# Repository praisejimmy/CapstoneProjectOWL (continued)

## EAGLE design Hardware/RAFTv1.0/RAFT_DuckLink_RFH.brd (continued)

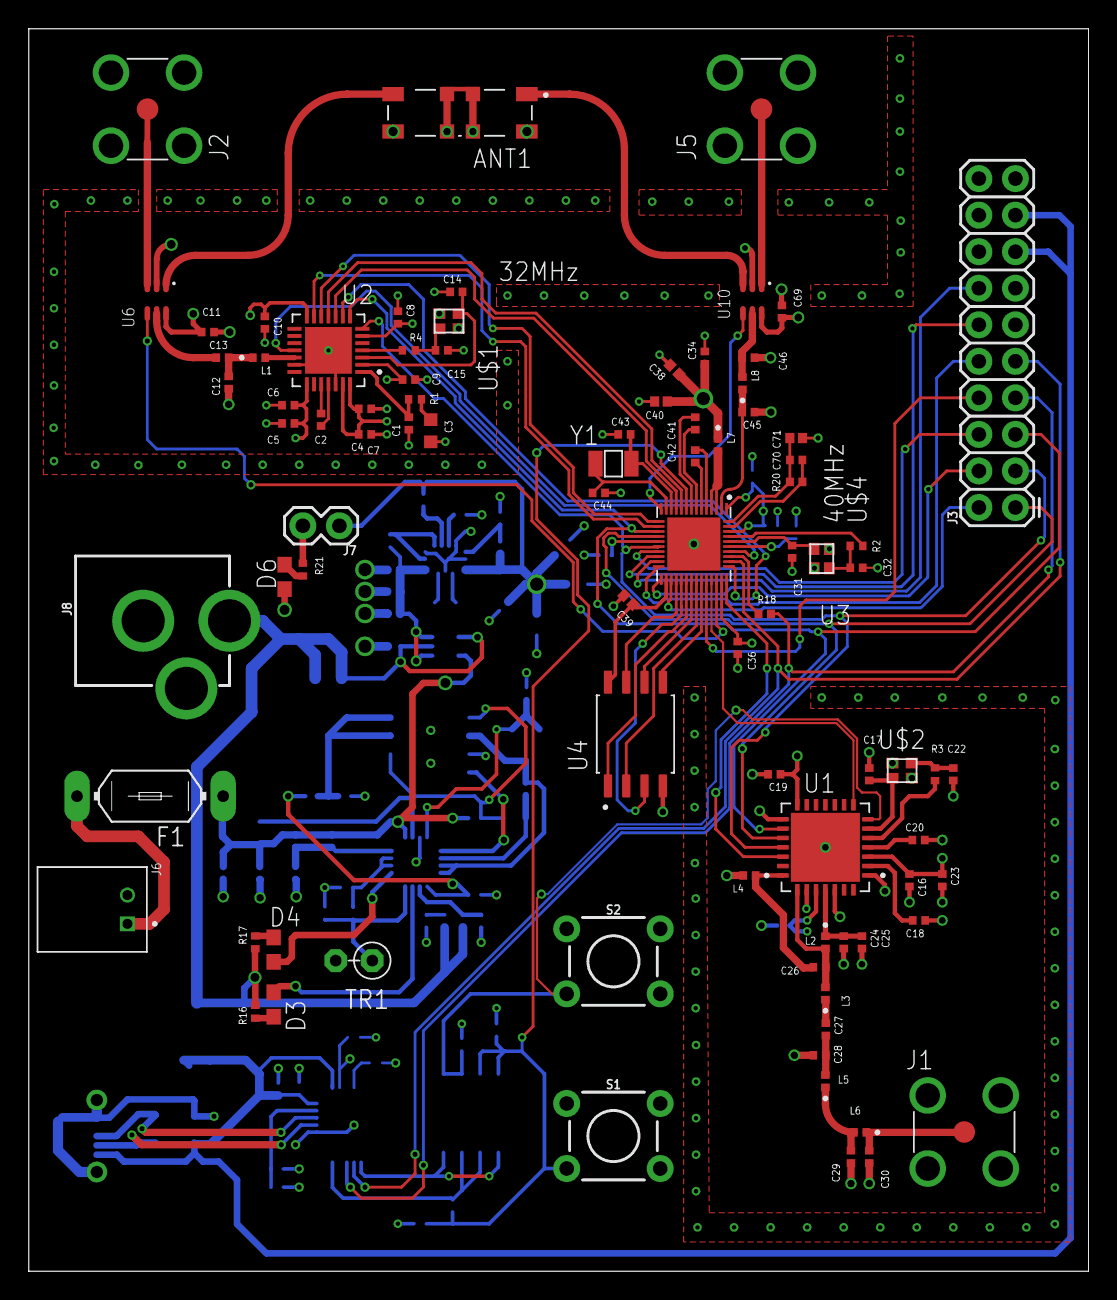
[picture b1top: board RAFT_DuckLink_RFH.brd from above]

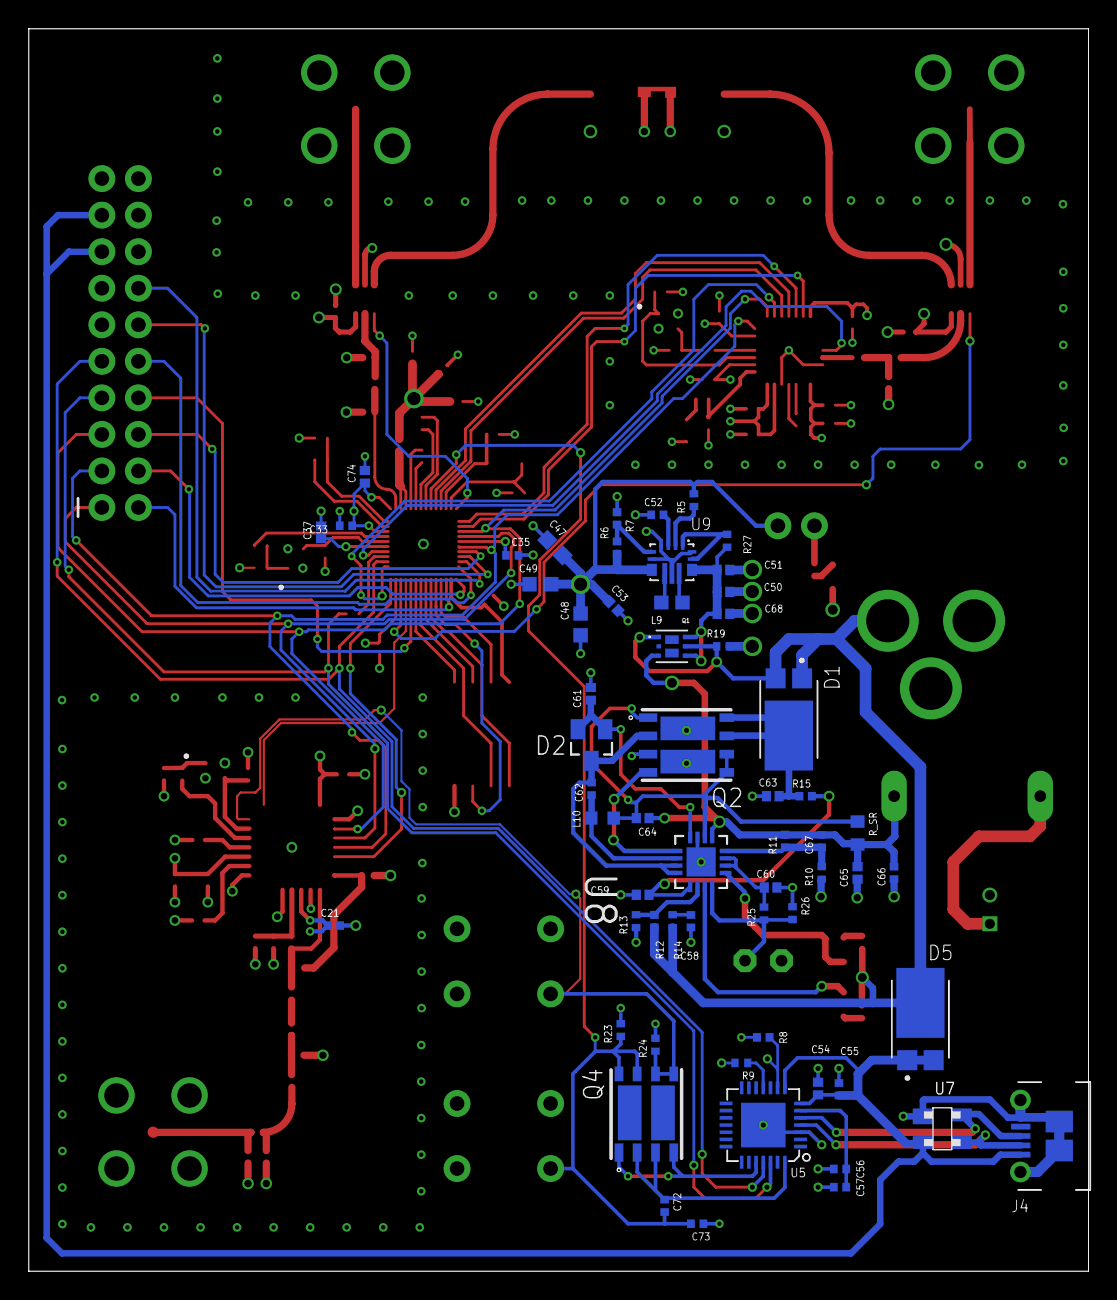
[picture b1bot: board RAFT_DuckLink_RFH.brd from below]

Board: 4 copper layers, 73.7 x 86.4 mm, 147 parts (60 on the bottom side), 111 nets.

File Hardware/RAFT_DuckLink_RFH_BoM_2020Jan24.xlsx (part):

Qty | Value | Device | Package | Ref Des | Description | DIGI-KEY_PART_NUMBER | DIGI-KEY_PURCHASE_URL | MF | MPN | PACKAGE.1
18 | 0.1uF | GCM155R71C104KA55J | CAPC1005X55N | C4, C6, C7, C8, C9, C10, C16, C18, C19, C20, C21, C34, C35, C36, C52, C55, C56,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 | Cap Ceramic 0.1uF 16V X7R 10% Pad SMD 0402 125Â°C Automotive T/R | 490-7998-1-ND | https://www.digikey.com/product-detail/en/murata-electronics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 | Murata | GCM155R71C104KA55J | 1005 Taiyo Yuden
3 | 0R | CRCW04020000Z0ED | RESC1005X40N | R2, R3, R4 | RESISTOR, 0402, 0R, FULL REEL | 541-0.0JCT-ND | https://www.digikey.com/product-detail/en/vishay-dale/CRCW04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 | Vishay | CRCW04020000Z0ED | 1005 Panasonic Electronic Components
4 | 1.0uF | GCM155C71A105KE38D | CAPC1005X70N | C54, C59, C60, C61 | Cap Ceramic 1uF 10V X7S 10% Pad SMD 0402 125C Automotive T/R |  |  | Murata | GCM155C71A105KE38D | 1005 Murata
1 | 1.5pF | GCM1555C1H1R5JA16D | CAPC1005X55N | C26 | CAP AUTO-GRADE 1.5PF 50VDC C0G 5% SMD 0402 | 490-16452-1-ND | https://www.digikey.com/product-detail/en/murata-electronics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 | Murata Electronics | GCM1555C1H1R5JA16D | 1005 Taiyo Yuden
1 | 1.5uH | LQM18PN1R5MFRL | INDC1608X95N | L9 | FIXED IND 1.5UH 800MA 288 MOHM | 490-17890-1-ND | https://www.digikey.com/product-detail/en/murata-electronics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 | Murata | LQM18PN1R5MFRL | 1608 Murata
1 | 1.7pF | GCM1555C1H1R7CA16D | CAPC1005X55N | C12 | CAP CER 1.7PF 50V NP0 0402 | GCM1555C1H1R7CA16D-ND | https://www.digikey.com/product-detail/en/murata-electronics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 | Murata | GCM1555C1H1R7CA16D | 1005 Taiyo Yuden
1 | 1.8pF | GCM1555C1H1R8CA16D | CAPC1005X55N | C30 | CAP AUTO-GRADE 1.8PF 50VDC C0G 0.25PF SMD 0402 | 490-17746-1-ND | https://www.digikey.com/product-detail/en/murata-electronics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 | Murata Electronics | GCM1555C1H1R8CA16D | 1005 Taiyo Yuden
1 | 10 | CRCW040210R0JNEDC | RESC1005X35N | R15 |  | 541-4122-1-ND | https://www.digikey.com/product-detail/en/vishay-dale/CRCW04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 | Vishay | CRCW040210R0JNEDC | 1005 Yageo
3 | 100k | CRCW0402100KFKED | RESC1005X40N | R19, R5, R10 | RES, THICK FILM, 100K, 1%, 0.063W, 0402 | 541-100KLCT-ND | https://www.digikey.com/product-detail/en/vishay-dale/CRCW04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 | Vishay | CRCW0402100KFKED | 1005 Panasonic Electronic Components
2 | 100pF | GCM1555C1H101JA16D | CAPC1005X55N | C5, C33 | Cap Ceramic 100pF 50V C0G 10% Pad SMD 0402 125Â°C Automotive T/R | 490-10669-1-ND | https://www.digikey.com/product-detail/en/murata-electronics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 | Murata | GCM1555C1H101JA16D | 1005 Taiyo Yuden
3 | 10K | CRCW040210K0JNED | RESC1005X40N | R16, R17, R9 | RES, THICK FILM, 10K, 5%, 0.063W, 0402, | 541-10KJCT-ND | https://www.digikey.com/product-detail/en/vishay-dale/CRCW04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 | Vishay Dale | CRCW040210K0JNED | 1005 Panasonic Electronic Components
3 | 10nF | GCM155R71H103KA55D | CAPC1005X55N | C14, C15, C25 | 10000pF Â±10% 50V Ceramic Capacitor X7R 0402 (1005 Metric)
1 | 10nH | LQG15HS10NJ02D | INDC1005X55N | L3 | Ind RF Chip Multi-Layer 10nH 5% 100MHz 8Q-Factor Air 300mA 0402 Paper T/R | 490-2623-1-ND | https://www.digikey.com/product-detail/en/murata-electronics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 | Murata | LQG15HS10NJ02D | 1005 Murata
8 | 10uF | GRM155C80J106ME11D | CAPC1005X70N | C40, C50, C51, C53, C63, C64, C65, C68 | 10µF ±20% 6.3V Ceramic Capacitor X6S 0402 (1005 Metric) | 490-13233-1-ND | https://www.digikey.com/product-detail/en/murata-electronics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 | Murata Electronics | GRM155C80J106ME11D | 1005 Murata
1 | 10uH | LQM18FN100M00D | INDC1608X90N | L10 | Inductor Power Chip Shielded Multi-Layer 10uH 20% 1MHz Ferrite 50mA 1.17Ohm DCR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 | 490-4025-1-ND | https://www.digikey.com/product-detail/en/murata-electronics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 | Murata Electronics | LQM18FN100M00D | 1608 Murata
1 | 150k | CRCW0402150KFKEDC | RESC1005X35N | R7 |  | 541-4008-1-ND | https://www.digikey.com/product-detail/en/vishay-dale/CRCW04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 | Vishay Dale | CRCW0402150KFKEDC | 1005 Yageo
1 | 15K | CRCW040215K0JNED | RESC1005X40N | R1 | Res Thick Film 0402 15K Ohm 5% 1/16W Â±200ppm/Â°C Molded SMD SMD Paper T/R | 541-15KJCT-ND | https://www.digikey.com/product-detail/en/vishay-dale/CRCW04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 | Vishay Dale | CRCW040215K0JNED | 1005 Panasonic Electronic Components
9 | 15pF | GCM1555C1H150JA16D | CAPC1005X55N | C1, C17, C22, C31, C32, C43, C44, C45, C46 | Cap Ceramic 15pF 50V C0G 5% Pad SMD 0402 125C Automotive T/R | 490-11147-1-ND | https://www.digikey.com/product-detail/en/murata-electronics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 | Murata | GCM1555C1H150JA16D | 1005 Taiyo Yuden
2 | 1nF | GCM155R71H102KA37D | CAPC1005X55N | C11 | Cap Ceramic 0.001uF 50V X7R 10% Pad SMD 0402 125C Automotive T/R | 490-4761-1-ND | https://www.digikey.com/product-detail/en/murata-electronics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 | Murata | GCM155R71H102KA37D | 1005 Taiyo Yuden
3 | 1uF | GCM155C71A105KE38D | CAPC1005X70N | C37, C38, C39 | Cap Ceramic 1uF 10V X7S 10% Pad SMD 0402 125C Automotive T/R | 490-13409-1-ND | https://www.digikey.com/product-detail/en/murata-electronics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 | Murata | GCM155C71A105KE38D | 1005 Murata
1 | 2.2uF | GRM155D80J225ME95D | CAPC1005X55N | C58 | CAP CER 2.2UF 6.3V X6T 0402 | 490-10450-1-ND | https://www.digikey.com/product-detail/en/murata-electronics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 | Murata | GRM155D80J225ME95D | 1005 Taiyo Yuden
1 | 20m | ERJ-3BWFR020V | RESC1608X55N | R_SR |  | P17461CT-ND | https://www.digikey.com/product-detail/en/panasonic-electron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 | Panasonic | ERJ-3BWFR020V | 1608 Panasonic Electronic Components
1 | 22pF | GCM1555C1H220JA16J | CAPC1005X55N | C67 | Cap Ceramic 22pF 50V C0G 5% Pad SMD 0402 125C Automotive T/R | 490-17747-1-ND | https://www.digikey.com/product-detail/en/murata-electronics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 | Murata | GCM1555C1H220JA16J | 1005 Taiyo Yuden
3 | 22uF | GRM188R60J226MEA0D | CAPC1608X100N | C47, C48, C49 | Cap Ceramic 22uF 6.3V X5R 20% Pad SMD 0603 85Â°C T/R | 490-7611-1-ND | https://www.digikey.com/product-detail/en/murata-electronics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 | Murata | GRM188R60J226MEA0D | 1608 Murata
2 | 270pF | GRM1555C1H271JA01D | CAPC1005X55N | C41, C42 | Multilayer Ceramic Capacitor, GRM Series, 270 pF, 5%, C0G / NP0, 50 V, 0402 [10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 | 490-1294-1-ND | https://www.digikey.com/product-detail/en/murata-electronics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 | Murata | GRM1555C1H271JA01D | 1005 Taiyo Yuden
1 | 2k | CRCW04022K00FKED | RESC1005X40N | R14 | RESISTOR, 0402, 2K, 1%, FULL REEL | 541-2.00KLCT-ND | https://www.digikey.com/product-detail/en/vishay-dale/CRCW04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 | Vishay Dale | CRCW04022K00FKED | 1005 Panasonic Electronic Components
1 | 2N7002 | 2N7002 | SOT23 | Q3 |  |  |  | STMicroelectronics | 2N7002 | SOT-23-3 Vishay
1 | 2nH | LQG15HN2N0C02D | INDC1005X55N | L7 | FIXED IND 2NH 900MA 90 MOHM | 490-15076-1-ND | https://www.digikey.com/product-detail/en/murata-electronics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 | Murata | LQG15HN2N0C02D | 1005 Murata
1 | 32.768kHz | FC-13532.768KA-AG0 | OSCCC150X320X80-2N | Y1 | FC-135 series 32.768kHz Â±20ppm Crystal 9pF 50 kOhms, -40Â°C ~ 85Â°C, Surface M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 |  |  | EPSON | FC-135R 32.7680KA-AC3 | SMD-2 Epson
2 | 32MHz | NX2016SA-32M | SMD-4 | U$1, U$2 | 32MHz Crystal 10pF 60 Ohms 4-SMD, No Lead
1 | 33nF | LQG15HS33NJ02D | INDC1005X55N | L2 | LQG Series 0402 33 nH Â±5 % Tol. 200 mA SMT High Frequency Multilayer Inductor | 490-2629-1-ND | https://www.digikey.com/product-detail/en/murata-electronics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 | Murata | LQG15HS33NJ02D | 1005 Murata
1 | 33pF | GCM1555C1H330JA16D | CAPC1005X55N | C27 | 33pF Â±5% 50V Ceramic Capacitor C0G, NP0 0402 (1005 Metric) |  |  | Murata | GCM1555C1H330JA16D | 1005 Taiyo Yuden
1 | 36k | CRCW040236K0FKED | RESC1005X40N | R13 | Surface Mount Thick Film Resistor, AEC-Q200 CRCW Series, 36 kohm, 63 mW, - 1%, 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 | 541-36.0KLCT-ND | https://www.digikey.com/product-detail/en/vishay-dale/CRCW04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 | Vishay | CRCW040236K0FKED | 1005 Panasonic Electronic Components
1 | 4.7k | CRCW04024K70JNEDC | RESC1005X35N | R8 | D10/CRCW0402-C 200 4K7 5% ET7 | 541-3974-1-ND | https://www.digikey.com/product-detail/en/vishay-dale/CRCW04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 | Vishay | CRCW04024K70JNEDC | 1005 Yageo
2 | 4.7pF | GCM1555C1H4R7CA16D | CAPC1005X55N | C28, C29 | Cap Ceramic 4.7pF 50V C0G 0.25pF SMD 0402 125Â°C Paper T/R | 490-12652-1-ND | https://www.digikey.com/product-detail/en/murata-electronics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 | Murata Electronics | GCM1555C1H4R7CA16D | 1005 Taiyo Yuden
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
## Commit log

2019-11-14 Initial commit, added separate folders for firmware and hardware design
2019-11-21 Hardware v1.0 project created
2019-12-03 added datasheets, libraries for some modules, removed epf (hopefully that wont affect anything)
2019-12-09 lora and gps schematics
2019-12-12 finalized gps. ref design for lora. renamed some libraries. added datasheets and started mcu schematic
2019-12-12 changed more libraries. replaced eeprom and flash mem, added datasheets
2019-12-28 finalized universal LoRa schematic. started power schematic. renamed schematics
2019-12-28 rerouted lora rf selector, removed unnecessary resistor
2020-01-08 lora rfh changed to low power mode. begin schematic for pa/rfl/rfh universal module
2020-01-10 started MCU layout. added supply library
2020-01-11 Deleted bq24630 datasheet
    Not moving forward w/ this component
2020-01-11 Added bq24650 MPPT Solar Charger datasheet
2020-01-13 Added ST1L08SPU33R
    3.3V Step Down
2020-01-13 Added Noah Schematics folder and Charger schematic for review
    Charger: Added missing components, renamed each component to coincide with datasheet example. Note, most of the previous components placed before my work are 0805 sizing so if the goal is 0402 then w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
2020-01-14 Removed old 3V3 regulator datasheet
2020-01-14 Added new 3V3 LDO datasheet
2020-01-14 started 0420 footprint conversion
2020-01-14 datasheet for usb to uart bridge
2020-01-15 Added 3V3 Regulator Schematic
2020-01-15 Added UART_Bridge Schematic
2020-01-15 updated libraries, started replacing components with model specified parts (gps 99% complete)
2020-01-15 this didnt work well. heres the new library
2020-01-15 main project file
2020-01-15 Replacing bq sch
2020-01-15 Updated Charger Schematic
    Updated components to be 0402 PACKAGES
2020-01-15 Added PDF versions of schematics just in case
2020-01-16 added another part and personal branch
2020-01-16 Initial code push
2020-01-17 Updated UART Bridge with specific components
2020-01-17 Removed old LDO sch
2020-01-17 Removed old LDO pdf
2020-01-17 Removed charger PDF
2020-01-17 added more parts. completed gps, lora
2020-01-17 Added updated charger pdf w/ components
2020-01-17 Added updated Charger with specified components
2020-01-17 Updated charger sch and pdf with specific components
2020-01-17 Updated charger sch and pdf w/ specific components
2020-01-17 Updated charger sch w/ specified components
    Getting upload failures so trying one file at a time
2020-01-17 Updated charger sch w/ components
2020-01-17 charger pdf w/ components
2020-01-17 remove old LDO
2020-01-17 Added TPS63060DSCR
2020-01-17 Updated schems w/ specific components
2020-01-17 started mcu. added 1.8v source for vddsdio
2020-01-17 more for mcu
2020-01-20 mcu completed
2020-01-20 remove old schematic
2020-01-20 added all designs to DuckLink schematic. renamed library
2020-01-22 replaced flash datasheet with correct one
2020-01-23 Removed old TPS63060DSCR regulator datasheet
2020-01-23 Add new TPS63070 3V3 regulator datasheet
2020-01-23 Remove old regulator PDF
2020-01-23 Remove old regulato schematic
2020-01-23 Added new TPS63070 3V3 Regulator Sch and PDF
2020-01-23 added load sharing system
2020-01-23 consolidated components
2020-01-23 eagle project file with libraries
2020-01-25 CAP connection and 2G4 antenna switch for MCU
2020-01-25 fixed component inconsistencies
2020-01-29 final gpio connections
2020-01-30 fixed uart, updated pins
2020-01-30 added libs for headers and switches (SparkFun). added sch page for io headers
2020-01-31 Initial firmware push, successfully compiled and flashed onto board
2020-02-03 GPIO and rst switches for cpu/usb-uart
2020-02-03 mirrored pin definitions spreadsheet into git
2020-02-03 typo/final edits
2020-02-03 PDF schematics
2020-02-04 replaced schematics for voltage regulator
2020-02-04 added internal antenna
2020-02-04 added second 3V3 and 5V gpio header rails
2020-02-06 Laid out initial structure for mama task
2020-02-06 add some notify bits
2020-02-06 Added H file for events
2020-02-06 Message Struct Added
2020-02-06 removed pull up resistors on uart present from designer confusion
2020-02-06 remove old schematics
2020-02-06 Test push
2020-02-06 Small change to test
2020-02-06 Changed message
2020-02-06 new jake
2020-02-06 Added JST Connector and V_BAT label
    changed VOUT_BATT -> V_BAT
2020-02-08 fixed ERC issues
2020-02-10 latest pdf export of schematics
2020-02-11 gitingnore for board files
2020-02-11 Added 2-pin JST connector... again
2020-02-11 1st attempt at mama main and duck.
2020-02-11 intial board layout files
2020-02-11 added uart to board layout
2020-02-13 added barrel jack. generated new PDFs
2020-02-13 battery charger/power distribution layouts
2020-02-18 Reverted back to C, Started lora task
2020-02-18 preliminary board layout
2020-02-18 power added to bottom layer
2020-02-20 nearly complete board layout
2020-02-20 pdf of current schematics
2020-02-23 mostly good board design
2020-02-23 fixed mosfet
2020-02-23 autorouted board
2020-02-23 nearly completed board routing. updated gitignore
2020-02-24 Created shared.h
2020-02-24 possible fixes for DFM
2020-02-27 complete routing
2020-02-27 fixed issue
2020-02-27 high-res pdf of current layout
2020-02-27 Cleaned up code, added CAST message Type
2020-02-28 pretty much final. added fuse and thermistor header
2020-02-28 fixed one thing probably broke several others
2020-03-02 added connection SX1276 interrupt (remapped SX_RST to button)
2020-03-05 Using new LoRa library. Added print statements
2020-03-05 Added Cmake File
2020-03-05 Wifi working
2020-03-10 Added functions to build lora packet, doesnt work yet
2020-03-10 Added prints
2020-03-20 Got wifi to compile
2020-03-20 Updated firmware README with install instructions
